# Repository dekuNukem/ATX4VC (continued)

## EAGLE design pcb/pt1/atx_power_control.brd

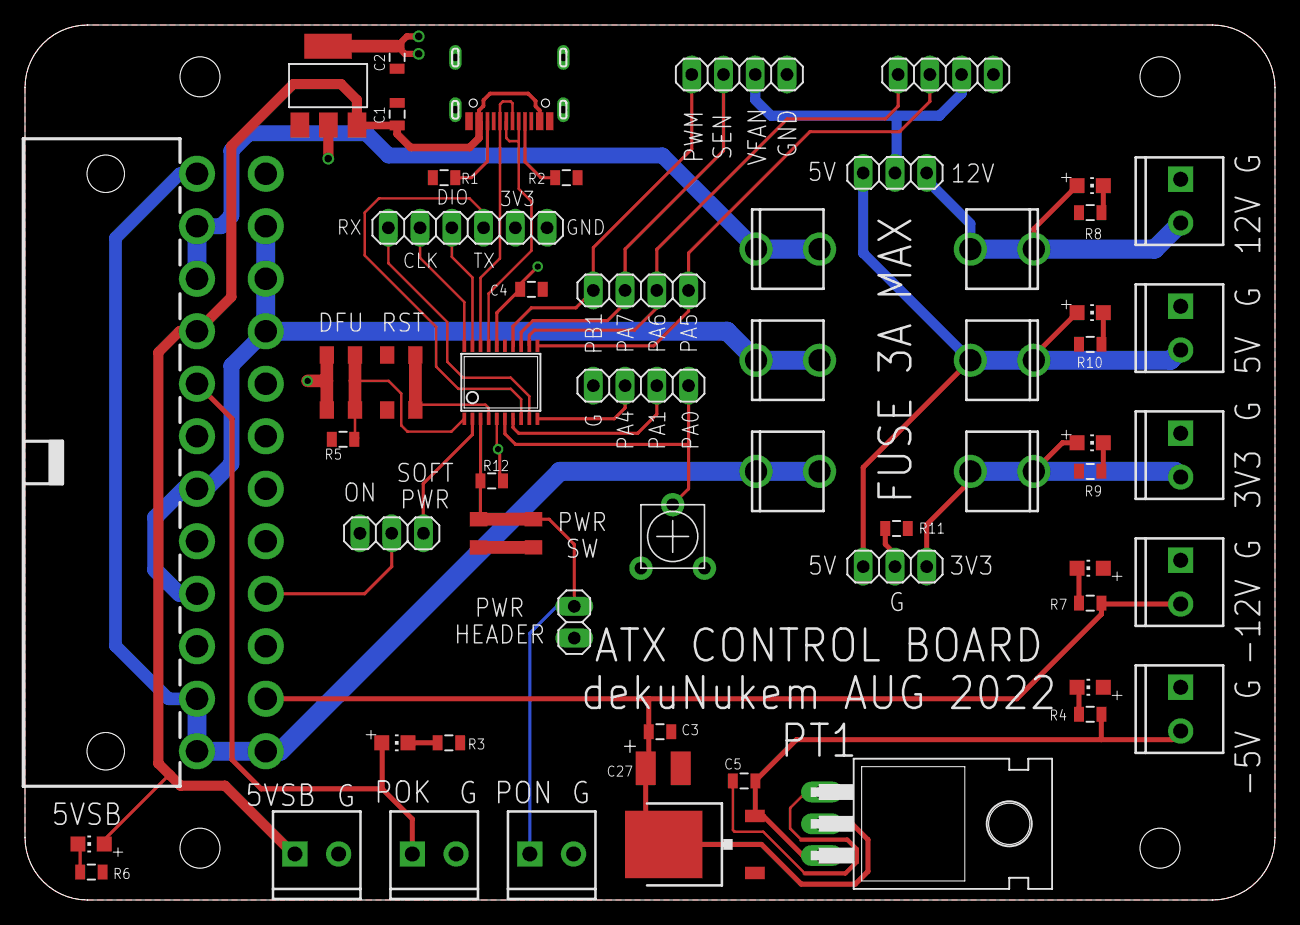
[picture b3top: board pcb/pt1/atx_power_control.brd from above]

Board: 2 copper layers, 100.0 x 70.0 mm, 59 parts (0 on the bottom side), 41 nets.

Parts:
C1, C2, C4, C5: 1uF; 0805@1
C3: 2.2uF; 0805@1
C27: 47uF; C1210
F1, F2, F3: FUSEX20MM; FUSE_5MM
IC1: TO220H
IC2: REG1117; SOT223
IC3: STM32F042F4; TSSOP20
IC4: MY_7905DT; ADAFRUIT_TO252
J1: ATX24RH; ATX24_RIGHT_ANGLE
J2, J3, J4, J6, J7, J8, J9, J10: SCREWTERMINAL-3.5MM-2
JP1, JP2, JP7, JP8: 1X04
JP3: 1X06
JP4, JP5, JP9: 1X03
JP6: 1X02
LED1, LED2, LED3, LED4, LED5, LED6, LED7: CHIP-LED0805
R1, R2, R5, R12: 5.1K; 0805
R3, R4, R6, R9, R10, R11: 1K; 0805
R7, R8: 5K; 0805
R13: TRIM_POT_PTH
SW1, SW3, SW4: 324_SW; 342_SWICH_FOOT
U2: USBC_16P; USBC_16P_FOOT
U$1, U$2, U$3, U$10: M3_MOUNTING_HOLE; M3_MOUNTING_HOLE_PACK

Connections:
+3V3: C2.2, C4.2, IC2.2, IC2.4, IC3.5, IC3.16, JP3.5, R12.2, R13.1, SW4.P$1, SW4.P$4
BUTTON1: IC3.4, SW3.P$2, SW3.P$3
BUTTON2: IC3.1, R5.2, SW4.P$2, SW4.P$3
GND: C1.1, C2.1, C3.1, C4.1, C5.1, C27.2, IC1.1, IC2.1, IC3.15, IC4.1, J1.3, J1.5, J1.7, J1.15, J1.17, J1.18, J1.19, J1.24, J2.1, J3.1, J4.1, J6.1, J7.1, J8.2, J9.2, J10.2, JP1.1, JP2.1, JP3.6, JP5.3, JP6.2, JP8.1, LED1.A, LED4.A, R1.2, R2.2, R3.1, R5.1, R6.1, R8.1, R9.1, R10.1, R11.1, R13.3, SW1.P$1, SW1.P$4, SW3.P$1, SW3.P$4, U2.A1B12, U2.B11A12, U2.P$13, U2.P$14, U2.P$15, U2.P$16
unnamed: LED3.C, R3.2
unnamed: C3.2, C27.1, IC1.2, IC4.3, J1.14, J3.2, R7.1
unnamed: IC3.20, JP3.2
unnamed: IC3.19, JP3.3
unnamed: LED1.C, R4.2
unnamed: IC3.8, JP3.4
unnamed: IC3.9, JP3.1
unnamed: LED4.C, R7.2
unnamed: LED5.C, R8.2
unnamed: F1.1, F1.2, J1.4, J1.6, J1.21, J1.22, J1.23
unnamed: C5.2, IC1.3, IC4.2, J4.2, R4.1
unnamed: F3.1, F3.2, J1.1, J1.2, J1.12, J1.13
unnamed: F2.3, F2.4, J1.10, J1.11
unnamed: IC3.11, JP1.3, JP7.4
unnamed: F1.3, F1.4, J7.2, JP4.1, JP9.1, LED7.A
unnamed: F2.1, F2.2, J6.2, JP4.3, LED5.A
unnamed: JP1.2, JP2.2, JP4.2
unnamed: LED6.C, R9.2
unnamed: F3.3, F3.4, J2.2, JP9.3, LED6.A
unnamed: LED7.C, R10.2
unnamed: IC3.12, JP1.4, JP7.3
unnamed: IC3.13, JP2.3, JP7.2
unnamed: IC3.14, JP2.4, JP7.1
unnamed: IC3.2, JP5.1
unnamed: J1.16, JP5.2
unnamed: IC3.3, J10.1, JP6.1, R12.1, SW1.P$2, SW1.P$3
unnamed: IC3.6, JP8.4, R13.2
unnamed: J1.8, J9.1, LED3.A
unnamed: LED2.C, R6.2
unnamed: IC3.7, JP8.3
unnamed: R1.1, U2.B5
unnamed: IC3.10, JP8.2
unnamed: R2.1, U2.A5
unnamed: JP9.2, R11.2
USB_DN: IC3.17, U2.A7, U2.B7
USB_DP: IC3.18, U2.A6, U2.B6
VCC: C1.2, IC2.3, J1.9, J8.1, LED2.A, U2.A4B9, U2.B4A9

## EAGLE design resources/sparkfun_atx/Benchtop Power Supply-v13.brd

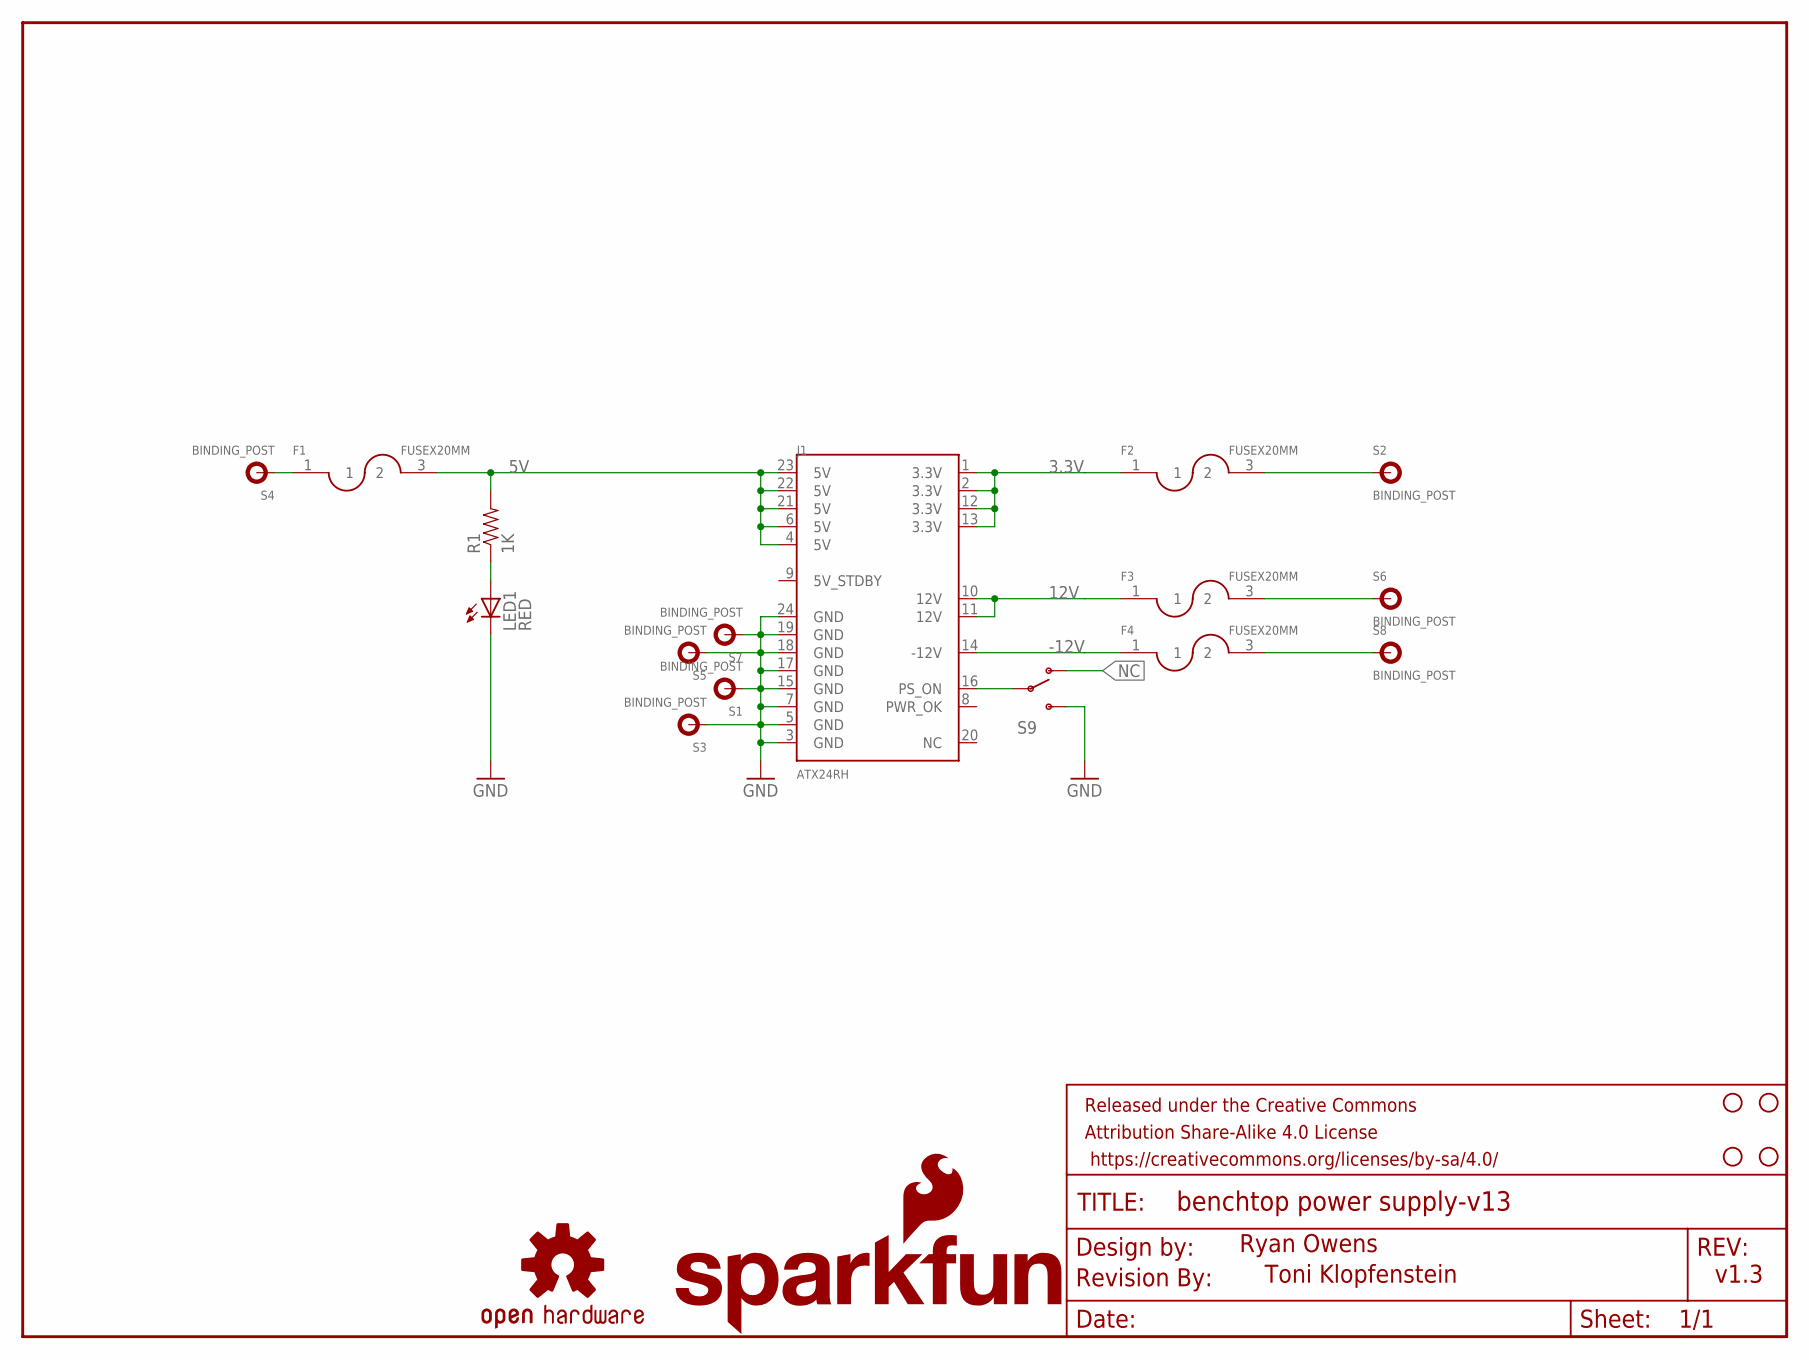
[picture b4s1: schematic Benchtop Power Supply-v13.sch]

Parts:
F1, F2, F3, F4: FUSEX20MM; FUSE_5MM
FRAME1: FRAME-LETTER; CREATIVE_COMMONS
J1: ATX24RH; ATX24_RIGHT_ANGLE
JP1: SFE_LOGO_NAME_FLAME.3_INCH; SFE_LOGO_NAME_FLAME_.3
JP2, JP3, JP4, JP5: STAND-OFF
LED1: RED; LED5MM
LOGO1: OSHW-LOGOL; OSHW-LOGO-L
R1: 1K; AXIAL-0.3
S1, S2, S3, S4, S5, S6, S7, S8: BINDING_POST
S9: SWITCH-SPDTKIT; SWITCH-SPDT_KIT
U$1: REVISION

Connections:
3.3V: F2.1, J1.1 (3.3V), J1.2 (3.3V), J1.12 (3.3V), J1.13 (3.3V)
3.3V_P: F2.3 (2), S2.P$1
5V: F1.3 (2), J1.4 (5V), J1.6 (5V), J1.21 (5V), J1.22 (5V), J1.23 (5V), R1.P$2 (2)
5V_P: F1.1, S4.P$1
12V: F3.1, J1.10 (12V), J1.11 (12V)
12V_P: F3.3 (2), S6.P$1
-12V: F4.1, J1.14 (-12V)
-12V_P: F4.3 (2), S8.P$1
GND: J1.3 (GND), J1.5 (GND), J1.7 (GND), J1.15 (GND), J1.17 (GND), J1.18 (GND), J1.19 (GND), J1.24 (GND), LED1.K (C), S1.P$1, S3.P$1, S5.P$1, S7.P$1, S9.3 (S)
unnamed: LED1.A, R1.P$1 (1)
unnamed: J1.16 (PS_ON), S9.2
NC: S9.1 (O)

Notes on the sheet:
Ryan Owens
Toni Klopfenstein
v1.3

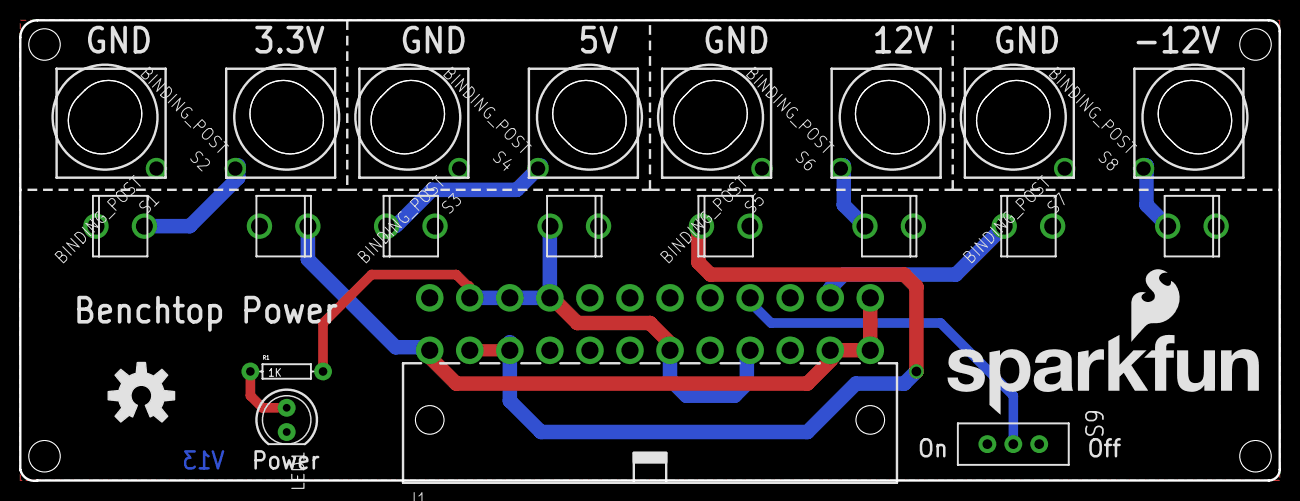
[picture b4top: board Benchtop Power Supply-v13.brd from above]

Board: 2 copper layers, 132.1 x 48.3 mm, 24 parts (0 on the bottom side), 11 nets.
